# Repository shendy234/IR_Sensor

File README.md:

# IR_Sensor
Schematic and PCB IR Sensor

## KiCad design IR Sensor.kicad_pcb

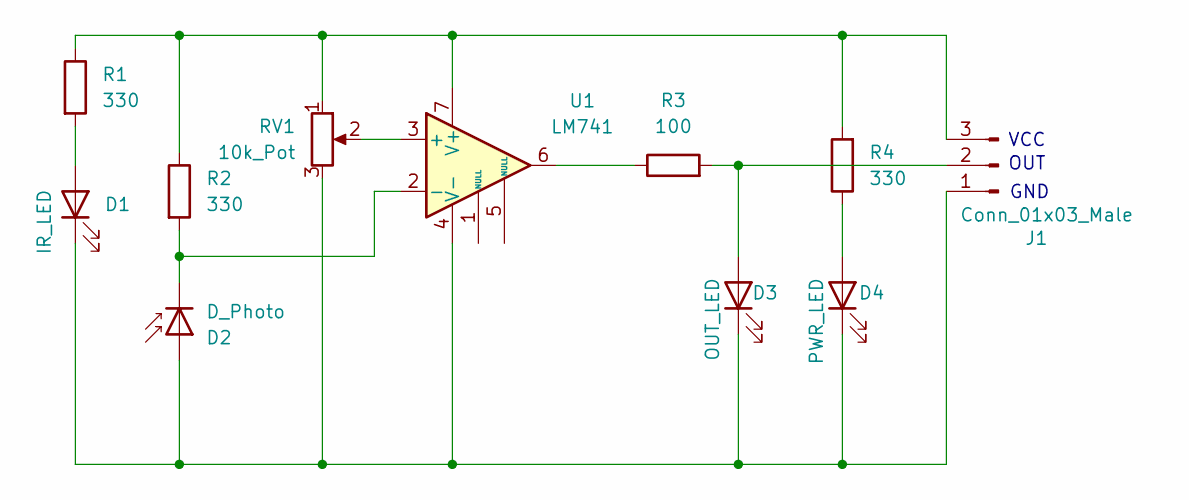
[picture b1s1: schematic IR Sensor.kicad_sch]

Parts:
D1: IR_LED; LED_D5.0mm_Horizontal_O1.27mm_Z3.0mm
D2: D_Photo; LED_D5.0mm_Horizontal_O1.27mm_Z3.0mm
D3: OUT_LED; LED_0805_2012Metric_Pad1.15x1.40mm_HandSolder
D4: PWR_LED; LED_0805_2012Metric_Pad1.15x1.40mm_HandSolder
J1: Conn_01x03_Male; PinHeader_1x03_P2.54mm_Horizontal
R1, R2, R4: 330; R_0805_2012Metric
R3: 100; R_0805_2012Metric
RV1: 10k_Pot; Potentiometer_ACP_CA9-V10_Vertical_Hole
U1: LM741; SOIC-8_3.9x4.9mm_P1.27mm

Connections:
unnamed: D1.2 (A), R1.2
unnamed: D1.1 (K), D2.2 (A), D3.1 (K), D4.1 (K), J1.1, RV1.3, U1.4 (V-)
unnamed: D2.1 (K), R2.2, U1.2 (-)
unnamed: D3.2 (A), J1.2, R3.2
unnamed: D4.2 (A), R4.1
unnamed: J1.3, R1.1, R2.1, R4.2, RV1.1, U1.7 (V+)
unnamed: R3.1, U1.6
unnamed: RV1.2, U1.3 (+)

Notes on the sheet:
OUT
VCC
GND

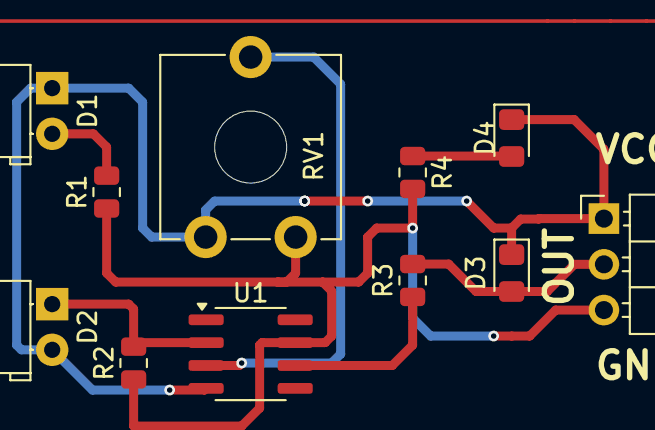
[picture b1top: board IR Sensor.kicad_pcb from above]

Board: 2 copper layers, 11 parts (0 on the bottom side), 8 nets.
